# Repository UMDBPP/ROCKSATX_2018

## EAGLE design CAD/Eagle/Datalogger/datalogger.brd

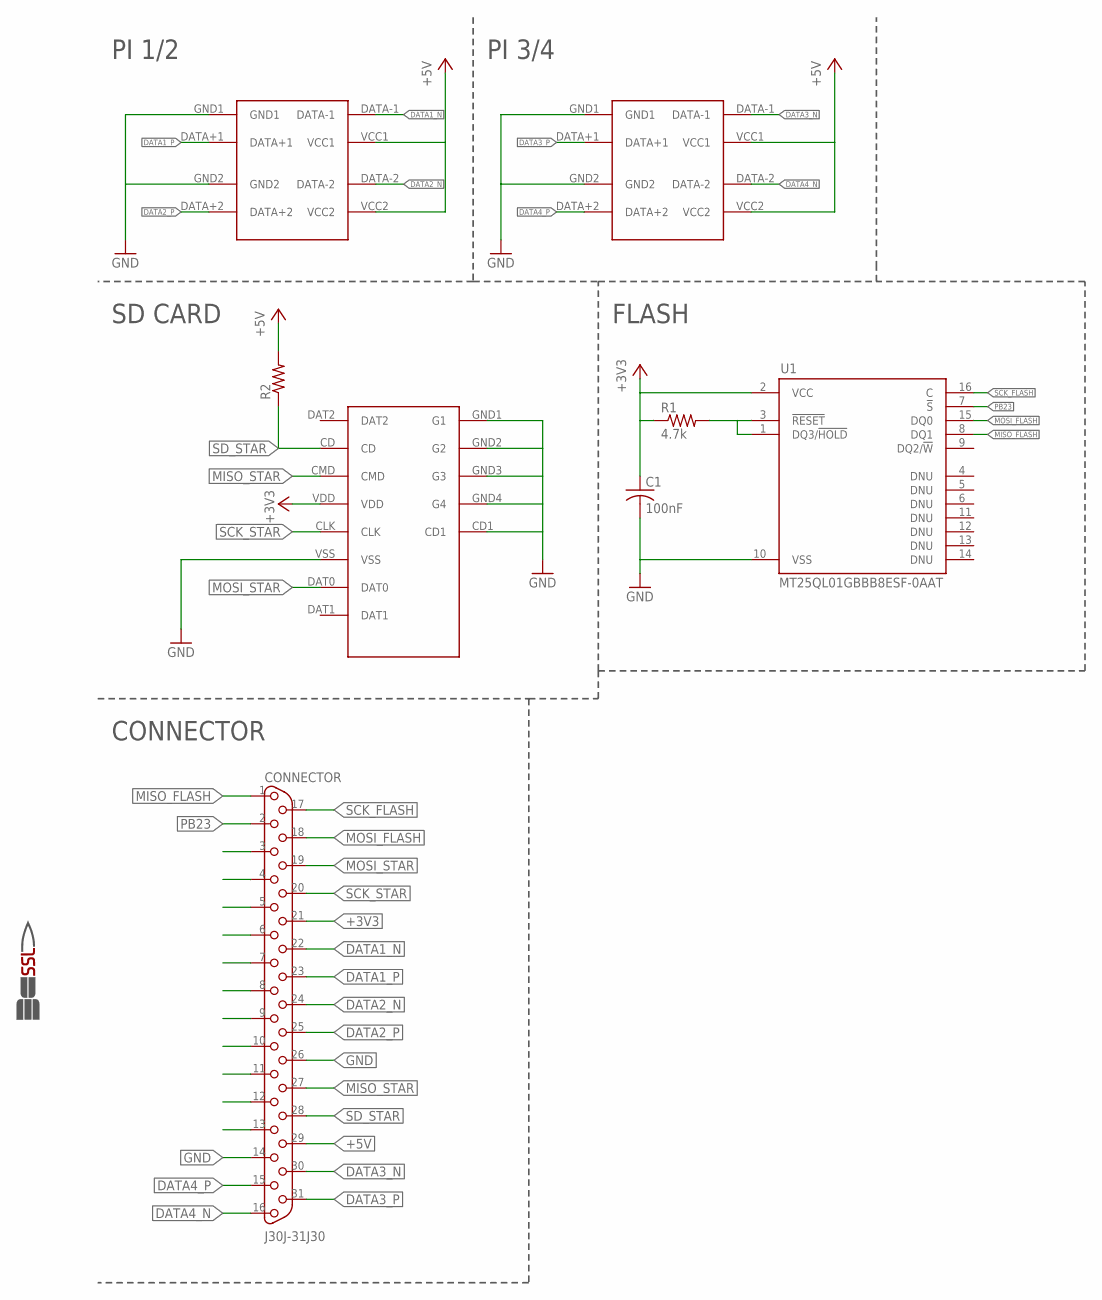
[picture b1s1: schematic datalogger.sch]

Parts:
C1: 100nF; C0603
CONNECTOR: J30J-31J30; ZKN-31-J30
R1: 4.7k; R0603
R2: R-US_R0603; R0603
U1: MT25QL01GBBB8ESF-0AAT; SOP2-16
U$1: MICRO_SD; MICRO_SD_HINGED
U$2, U$3: USB_A
U$4: SSL.3IN_SILK; SSL_SILK_.3IN

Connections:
+3V3: C1.1, CONNECTOR.21, R1.1, U1.2 (VCC), U$1.VDD
+5V: CONNECTOR.29, R2.2, U$2.VCC1, U$2.VCC2, U$3.VCC1, U$3.VCC2
DATA1_N: CONNECTOR.22, U$2.DATA-1
DATA1_P: CONNECTOR.23, U$2.DATA+1
DATA2_N: CONNECTOR.24, U$2.DATA-2
DATA2_P: CONNECTOR.25, U$2.DATA+2
DATA3_N: CONNECTOR.30, U$3.DATA-1
DATA3_P: CONNECTOR.31, U$3.DATA+1
DATA4_N: CONNECTOR.16, U$3.DATA-2
DATA4_P: CONNECTOR.15, U$3.DATA+2
GND: C1.2, CONNECTOR.14, CONNECTOR.26, U1.10 (VSS), U$1.CD1, U$1.GND1 (G1), U$1.GND2 (G2), U$1.GND3 (G3), U$1.GND4 (G4), U$1.VSS, U$2.GND1, U$2.GND2, U$3.GND1, U$3.GND2
MISO_FLASH: CONNECTOR.1, U1.8 (DQ1)
MISO_STAR: CONNECTOR.27, U$1.CMD
MOSI_FLASH: CONNECTOR.18, U1.15 (DQ0)
MOSI_STAR: CONNECTOR.19, U$1.DAT0
unnamed: R1.2, U1.1 (DQ3/!HOLD!), U1.3 (!RESET!)
PB23: CONNECTOR.2, U1.7 (!S!)
SCK_FLASH: CONNECTOR.17, U1.16 (C)
SCK_STAR: CONNECTOR.20, U$1.CLK
SD_STAR: CONNECTOR.28, R2.1, U$1.CD

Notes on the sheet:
PI 1/2
PI 3/4
SD CARD
CONNECTOR
FLASH

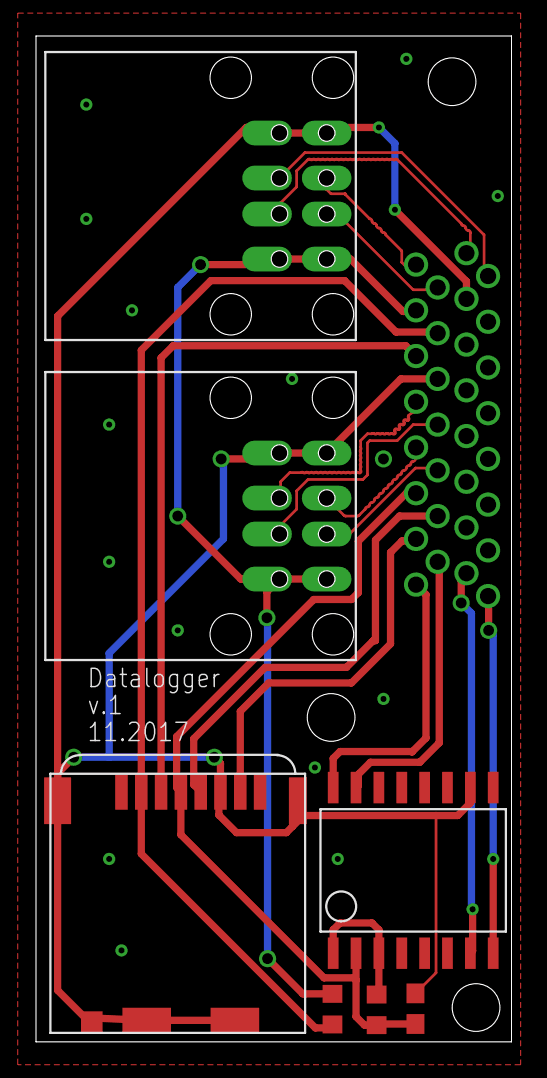
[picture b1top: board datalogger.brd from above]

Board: 2 copper layers, 26.4 x 55.9 mm, 9 parts (1 on the bottom side), 20 nets.

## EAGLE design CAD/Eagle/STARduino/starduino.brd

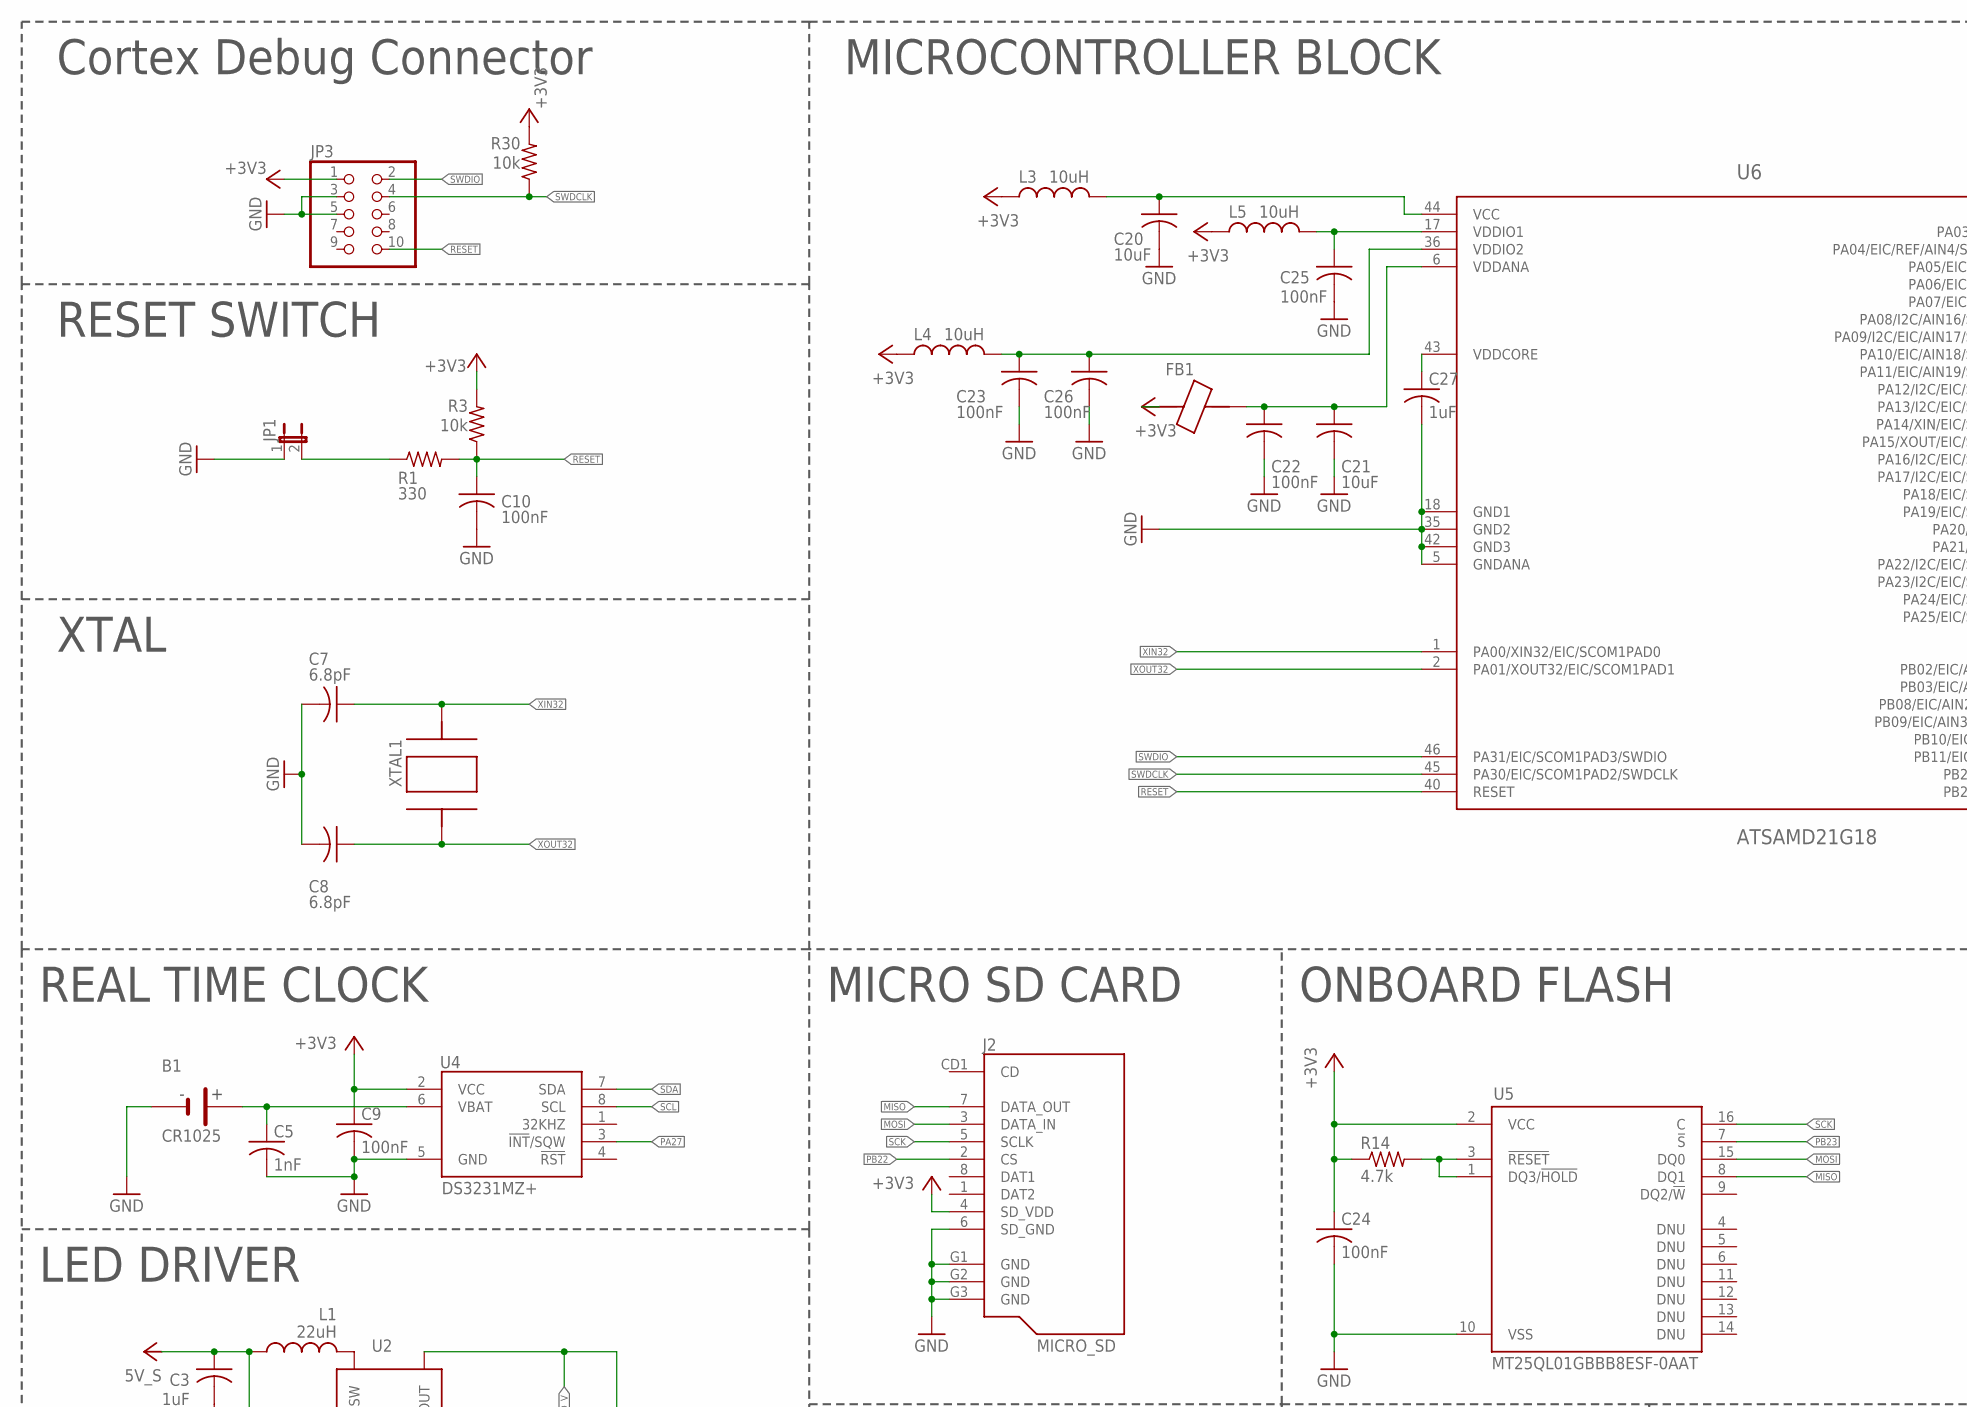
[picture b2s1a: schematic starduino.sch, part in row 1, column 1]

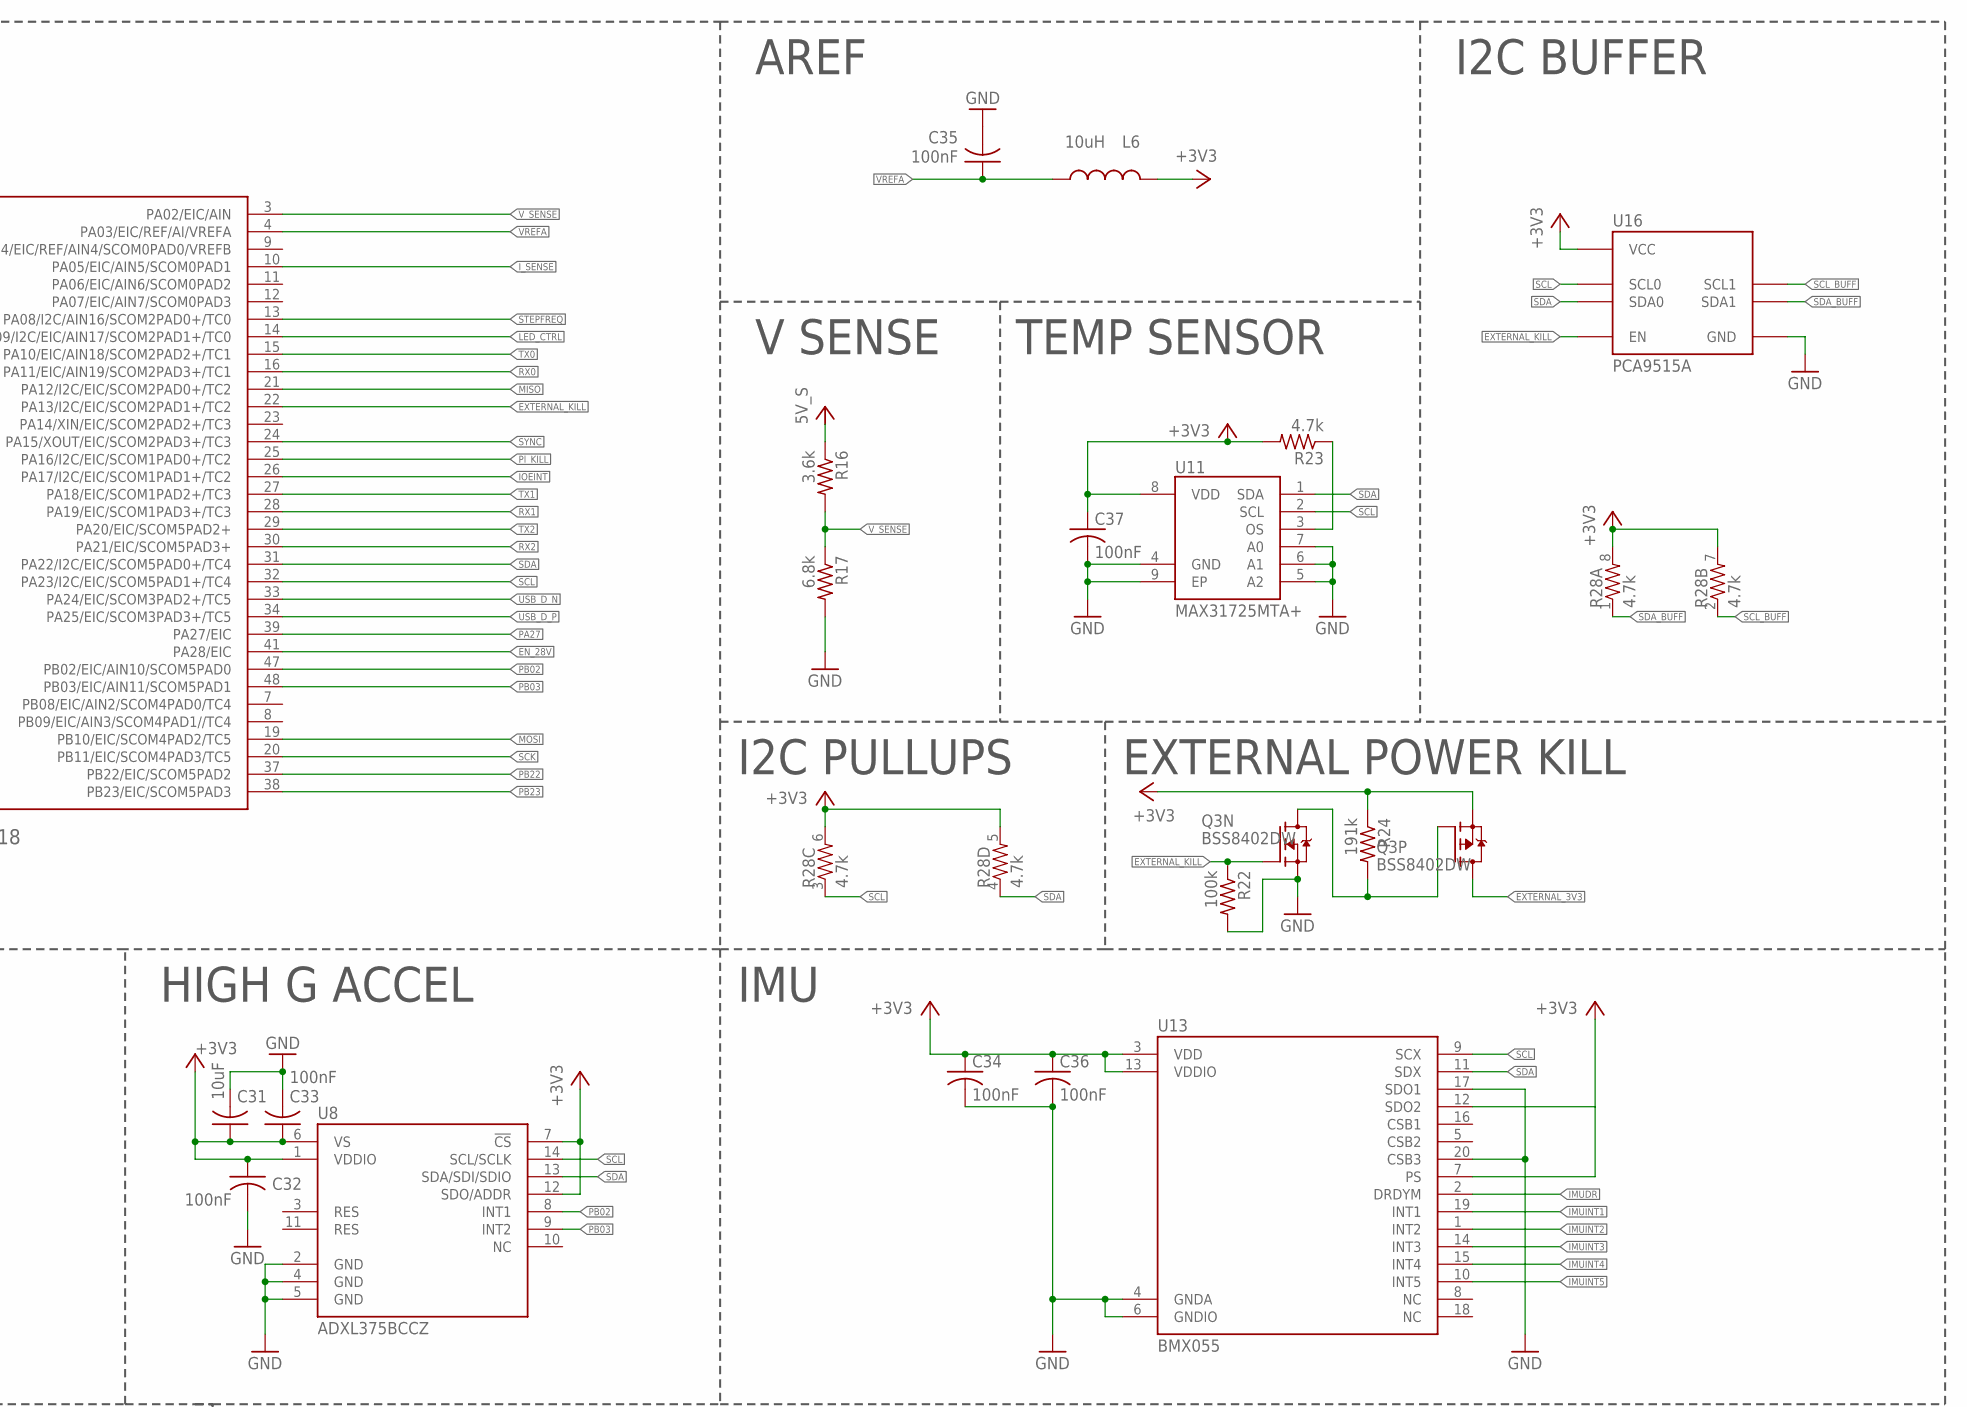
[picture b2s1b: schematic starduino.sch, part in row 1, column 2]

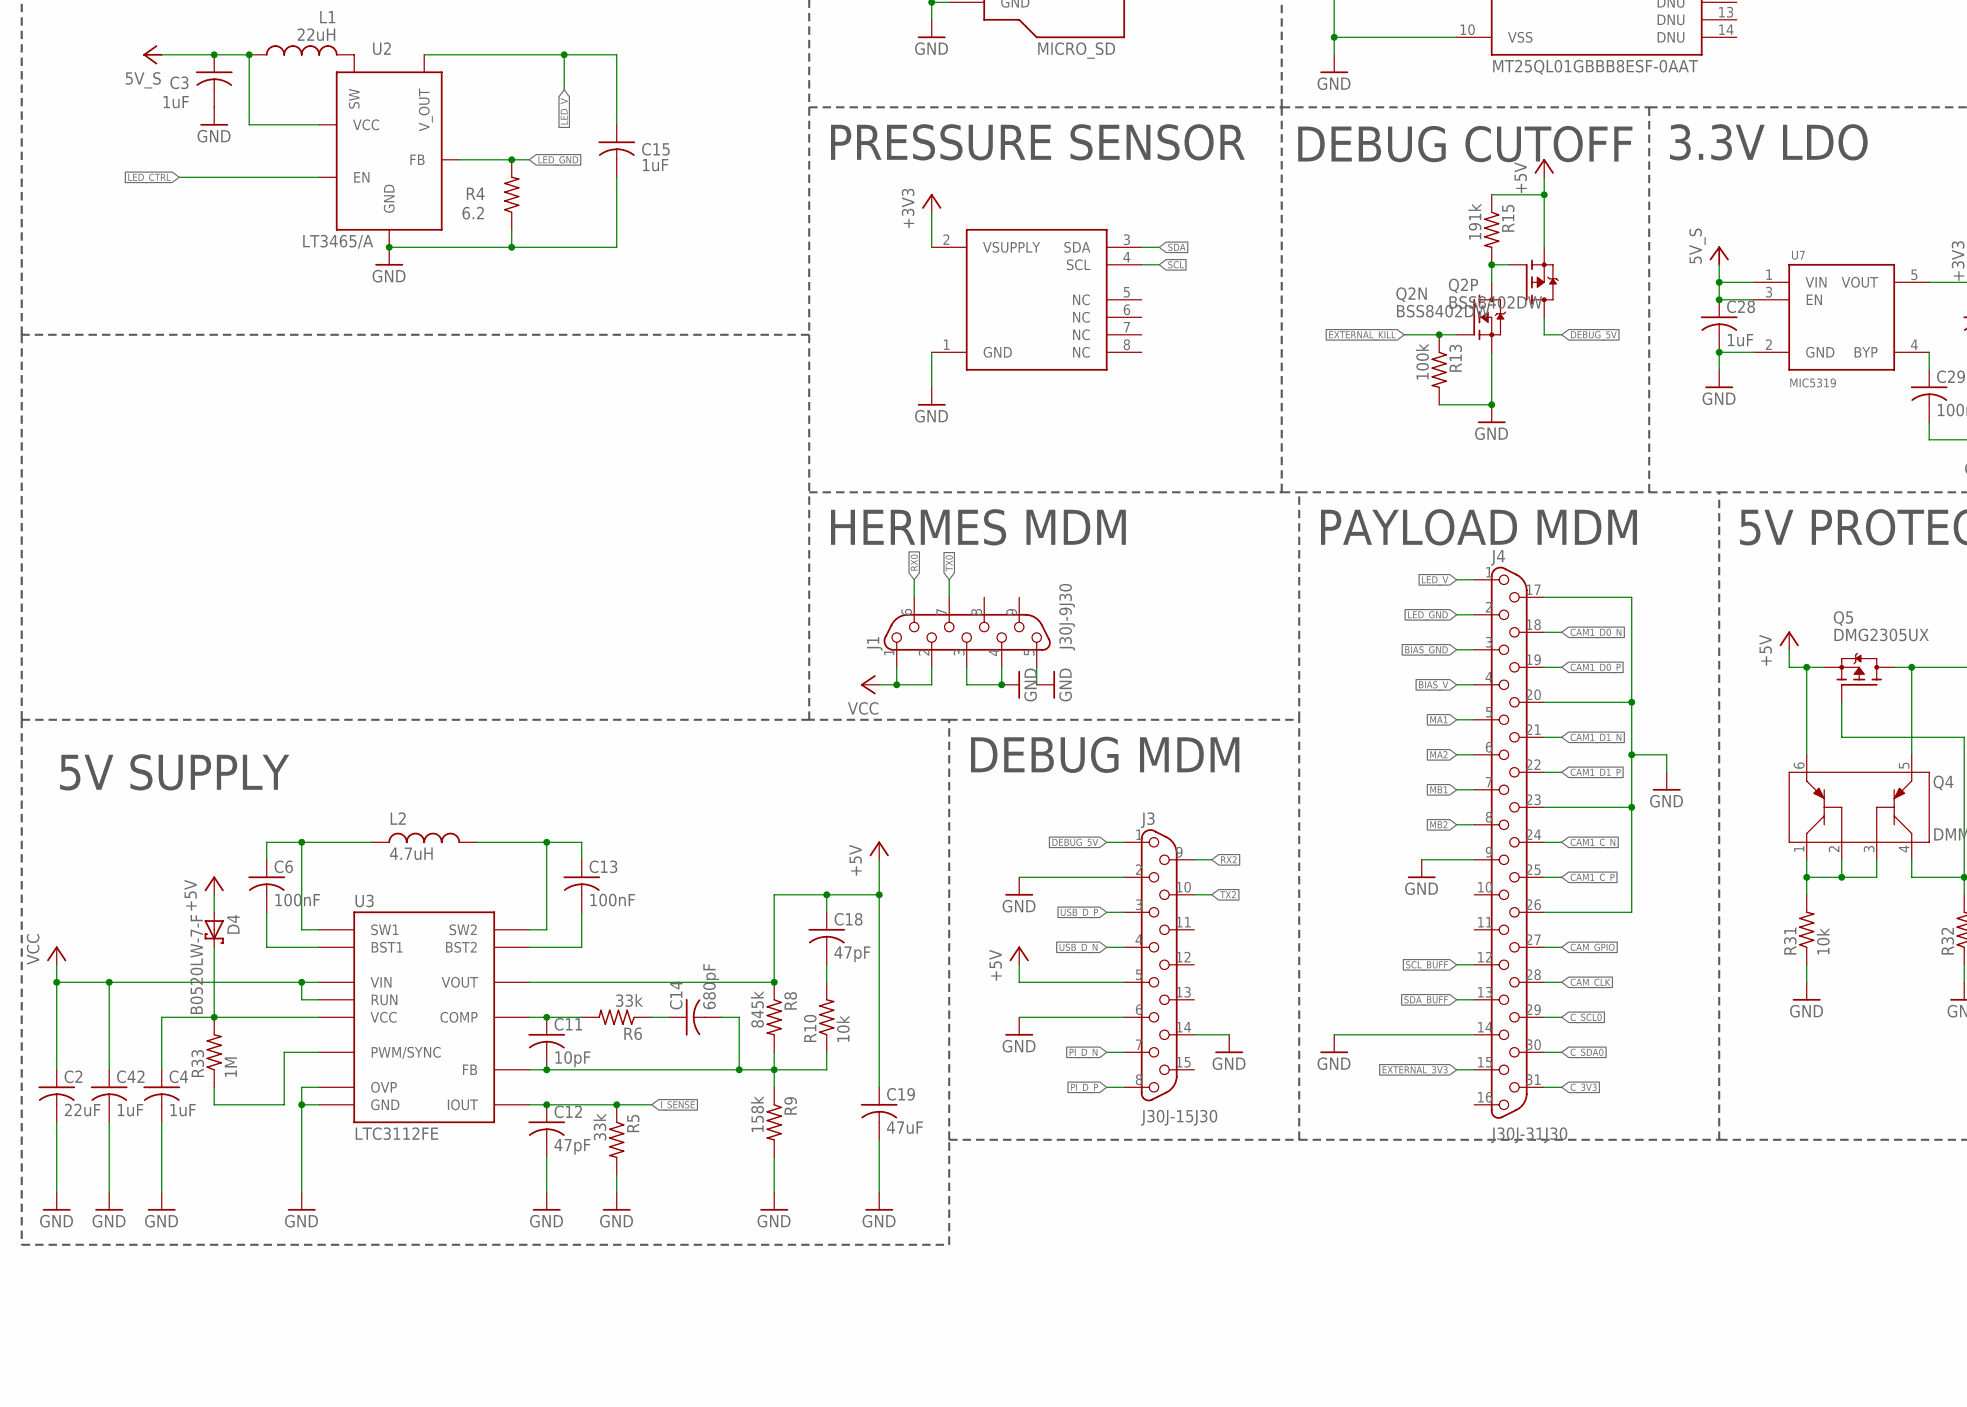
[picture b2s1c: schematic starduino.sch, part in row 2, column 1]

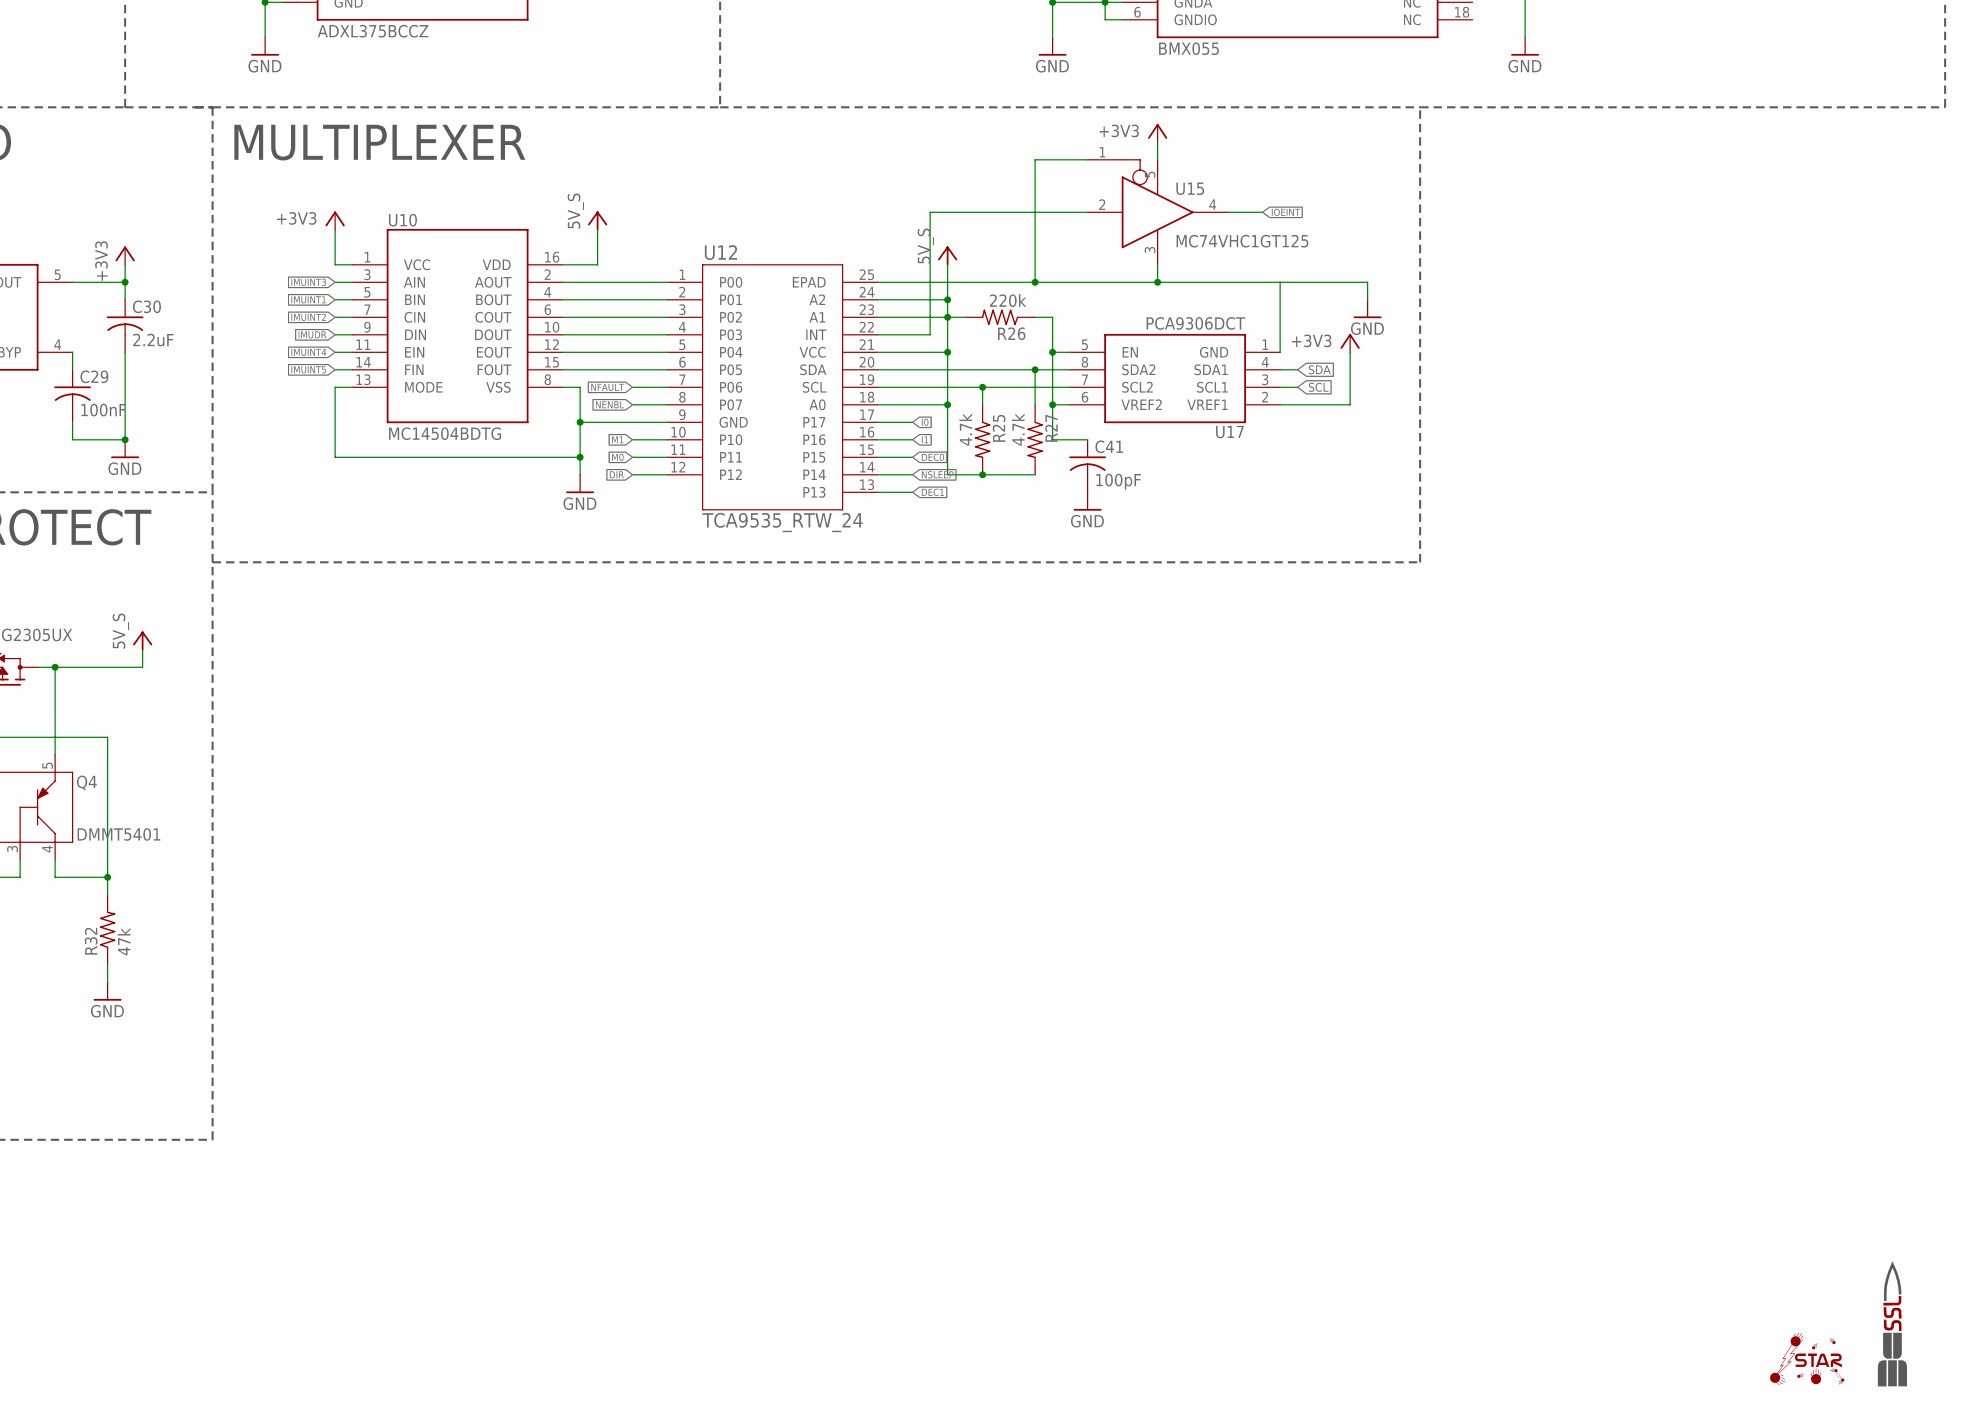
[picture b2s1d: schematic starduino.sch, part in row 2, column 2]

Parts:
B1: CR1025
C2: 22uF; C1206
C3, C4, C15, C27, C28, C42: 1uF; C0603
C5: 1nF; C0603
C6, C9, C10, C13, C22, C23, C24, C25, C26, C29, C32, C33, C34, C35, C36, C37: 100nF; C0603
C7, C8: 6.8pF; C0603
C11: 10pF; C0603
C12, C18: 47pF; C0603
C14: 680pF; C0603
C19: 47uF; C1210
C20, C21, C31: 10uF; C0603
C30: 2.2uF; C0603
C41: 100pF; C0603
D4: B0520LW-7-F; SOD123
FB1: BLM18KG221BH1D; 0603
J1: J30J-9J30; ZKN-9-J30
J2: MICRO_SD; MICROSD_PUSH_PUSH_AMPHENOL
J3: J30J-15J30; ZKN-15-J30
J4: J30J-31J30; ZKN-31-J30
JP1: JUMPER-2PTH; 1X02
JP3: PINHD-2X5; 2X05
L1: 22uH; VLF504012MT(TDK)
L2: 4.7uH; SRP5030
L3, L4, L5, L6: 10uH; 0603
Q2, Q3: BSS8402DW; SC70
Q4: DMMT5401; SOT-26
Q5: DMG2305UX; SOT23
R1: 330; R0603
R3, R10, R30, R31: 10k; R0603
R4: 6.2; R0603
R5, R6: 33k; R0603
R8: 845k; R0603
R9: 158k; R0603
R13, R22: 100k; R0603
R14, R23, R25, R27: 4.7k; R0603
R15, R24: 191k; R0603
R16: 3.6k; R0603
R17: 6.8k; R0603
R26: 220k; R0603
R28: 4.7k; 0603-ARV
R32: 47k; R0603
R33: 1M; R0603
U1: SSCMNNN015PA2A3; HSC-SMT-8
U2: LT3465/A; SOT23-6
U3: LTC3112FE; TSSOP20
U4: DS3231MZ+; SOIC-8
U5: MT25QL01GBBB8ESF-0AAT; SOP2-16
U6: ATSAMD21G18; 48-TQFP
U7: MIC5319; SOT23-5L
U8: ADXL375BCCZ; LGA-14
U10: MC14504BDTG; TSSOP16
U11: MAX31725MTA+; DFN-8
U12: TCA9535_RTW_24; RTW24_2P45X2P45
U13: BMX055; LGA-20
U15: MC74VHC1GT125; SC-70-5
U16: PCA9515A; TSSOP8
U17: PCA9306DCT; SSOP8
U$1: STAR; STAR_.3IN
U$2: SSL.3IN_SILK; SSL_SILK_.3IN
XTAL1: ABS07AIG-32.768KHZ-1-T; 2-SMD

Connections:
5V_S: C3.1, C28.1, L1.P$1 (1), Q4.5 (E2), Q5.3 (D), R16.1, R25.2, R26.2, R27.2, U2.5 (VCC), U7.1 (VIN), U7.3 (EN), U10.16 (VDD), U12.18 (A0), U12.21 (VCC), U12.23 (A1), U12.24 (A2)
+3V3: C9.1, C24.1, C30.1, C31.1, C32.1, C33.1, C34.1, C36.1, C37.1, FB1.1, J2.4 (SD_VDD), JP3.1, L3.1, L4.1, L5.1, L6.2, Q3.4 (S), R3.2, R14.1, R23.2, R24.1, R28.5 (2), R28.6 (2), R28.7 (2), R28.8 (2), R30.2, U1.2 (VSUPPLY), U4.2 (VCC), U5.2 (VCC), U7.5 (VOUT), U8.1 (VDDIO), U8.6 (VS), U8.7 (!CS!), U8.12 (SDO/ADDR), U10.1 (VCC), U11.8 (VDD), U13.3 (VDD), U13.7 (PS), U13.12 (SDO2), U13.13 (VDDIO), U15.5 (VIN), U16.P$8 (VCC), U17.2 (VREF1)
+5V: C18.1, C19.1, D4.A, J3.5, Q2.4 (S), Q4.6 (E1), Q5.2 (S), R8.1, R15.1, U3.9 (VOUT)
BIAS_GND: J4.3
BIAS_V: J4.4
CAM1_C_N: J4.24
CAM1_C_P: J4.25
CAM1_D0_N: J4.18
CAM1_D0_P: J4.19
CAM1_D1_N: J4.21
CAM1_D1_P: J4.22
CAM_CLK: J4.28
CAM_GPIO: J4.27
C_3V3: J4.31
C_SCL0: J4.29
C_SDA0: J4.30
DEBUG_5V: J3.1, Q2.3 (D)
DEC0: U12.15
DEC1: U12.13
DIR: U12.12
EN_28V: U6.41 (PA28/EIC)
EXTERNAL_3V3: J4.15, Q3.3 (D)
EXTERNAL_KILL: Q2.2 (G), Q3.2 (G), R13.1, R22.1, U6.22 (PA13/I2C/EIC/SCOM2PAD1+/TC2), U16.P$5 (EN)
FB_5: C11.2, C14.2, R8.2, R9.1, R10.1, U3.3 (FB)
GND: B1.3 (-), C2.2, C3.2, C4.2, C5.2, C7.2, C8.2, C9.2, C10.2, C12.2, C15.2, C19.2, C20.2, C21.2, C22.2, C23.2, C24.2, C25.2, C26.2, C27.2, C28.2, C29.2, C30.2, C31.2, C32.2, C33.2, C34.2, C35.2, C36.2, C37.2, C41.2, C42.2, J1.3, J1.4, J1.5, J2.6 (SD_GND), J2.G1 (GND), J2.G2 (GND), J2.G3 (GND), J3.2, J3.6, J3.14, J4.9, J4.14, J4.17, J4.20, J4.23, J4.26, JP1.1, JP3.3, JP3.5, Q2.1 (S), Q3.1 (S), R4.1, R5.2, R9.2, R13.2, R17.2, R22.2, R31.1, R32.1, U1.1 (GND), U2.2 (GND), U3.1 (GND), U3.4 (OVP), U3.10 (GND), U3.11 (GND), U3.20 (GND), U3.PAD (GND), U4.5 (GND), U5.10 (VSS), U6.5 (GNDANA), U6.18 (GND1), U6.35 (GND2), U6.42 (GND3), U7.2 (GND), U8.2 (GND), U8.4 (GND), U8.5 (GND), U10.8 (VSS), U10.13 (MODE), U11.4 (GND), U11.5 (A2), U11.6 (A1), U11.7 (A0), U11.9 (EP), U12.9 (GND), U12.25 (EPAD), U13.4 (GNDA), U13.6 (GNDIO), U13.17 (SDO1), U13.20 (CSB3), U15.1 (OE), U15.3 (GND), U16.P$4 (GND), U17.1 (GND)
I0: U12.17
I1: U12.16
IMUDR: U10.9 (DIN), U13.2 (DRDYM)
IMUINT1: U10.5 (BIN), U13.19 (INT1)
IMUINT2: U10.7 (CIN), U13.1 (INT2)
IMUINT3: U10.3 (AIN), U13.14 (INT3)
IMUINT4: U10.11 (EIN), U13.15 (INT4)
IMUINT5: U10.14 (FIN), U13.10 (INT5)
IOEINT: U6.26 (PA17/I2C/EIC/SCOM1PAD1+/TC2), U15.4 (Y)
I_SENSE: C12.1, R5.1, U3.8 (IOUT), U6.10 (PA05/EIC/AIN5/SCOM0PAD1)
LED_CTRL: U2.4 (EN), U6.14 (PA09/I2C/EIC/AIN17/SCOM2PAD1+/TC0)
LED_GND: J4.2, R4.2, U2.3 (FB)
LED_V: C15.1, J4.1, U2.1 (V_OUT)
M0: U12.11
M1: U12.10
MA1: J4.5
MA2: J4.6
MB1: J4.7
MB2: J4.8
MISO: J2.7 (DATA_OUT), U5.8 (DQ1), U6.21 (PA12/I2C/EIC/SCOM2PAD0+/TC2)
MOSI: J2.3 (DATA_IN), U5.15 (DQ0), U6.19 (PB10/EIC/SCOM4PAD2/TC5)
unnamed: Q4.4 (C2), Q5.1 (G), R32.2
unnamed: Q4.1 (C1), Q4.2 (B1), Q4.3 (B2), R31.2
unnamed: R33.1, U3.19 (PWM/SYNC)
unnamed: C25.1, L5.2, U6.17 (VDDIO1)
unnamed: C27.1, U6.43 (VDDCORE)
unnamed: R23.1, U11.3 (OS)
unnamed: JP1.2, R1.1
unnamed: B1.1 (+), B1.2 (+), C5.1, U4.6 (VBAT)
unnamed: C29.1, U7.4 (BYP)
unnamed: C21.1, C22.1, FB1.2, U6.6 (VDDANA)
unnamed: C14.1, R6.1
unnamed: C11.1, R6.2, U3.2 (COMP)
unnamed: C20.1, L3.2, U6.44 (VCC)
unnamed: L1.P$2 (2), U2.6 (SW)
unnamed: Q3.5 (G), Q3.6 (D), R24.2
unnamed: U10.2 (AOUT), U12.1 (P00)
unnamed: U10.4 (BOUT), U12.2 (P01)
unnamed: C23.1, C26.1, L4.2, U6.36 (VDDIO2)
unnamed: U12.22 (INT), U15.2 (A)
unnamed: U10.6 (COUT), U12.3 (P02)
unnamed: U10.10 (DOUT), U12.4 (P03)
unnamed: U10.12 (EOUT), U12.5 (P04)
unnamed: U10.15 (FOUT), U12.6 (P05)
unnamed: R14.2, U5.1 (DQ3/!HOLD!), U5.3 (!RESET!)
unnamed: R27.1, U12.20 (SDA), U17.8 (SDA2)
unnamed: R25.1, U12.19 (SCL), U17.7 (SCL2)
unnamed: C41.1, R26.1, U17.5 (EN), U17.6 (VREF2)
unnamed: Q2.5 (G), Q2.6 (D), R15.2
unnamed: C6.1, L2.P$1, U3.15 (SW1), U3.16 (SW1)
unnamed: C13.1, L2.P$2, U3.12 (SW2), U3.13 (SW2)
unnamed: C6.2, U3.17 (BST1)
unnamed: C13.2, U3.14 (BST2)
unnamed: C4.1, D4.C, R33.2, U3.18 (VCC)
unnamed: C18.2, R10.2
NENBL: U12.8 (P07)
NFAULT: U12.7 (P06)
NSLEEP: U12.14
PA27: U4.3 (!INT!/SQW), U6.39 (PA27/EIC)
PB02: U6.47 (PB02/EIC/AIN10/SCOM5PAD0), U8.8 (INT1)
PB03: U6.48 (PB03/EIC/AIN11/SCOM5PAD1), U8.9 (INT2)
PB22: J2.2 (CS), U6.37 (PB22/EIC/SCOM5PAD2)
PB23: U5.7 (!S!), U6.38 (PB23/EIC/SCOM5PAD3)
PI_D_N: J3.7
PI_D_P: J3.8
PI_KILL: U6.25 (PA16/I2C/EIC/SCOM1PAD0+/TC2)
RESET: C10.1, JP3.10, R1.2, R3.1, U6.40 (RESET)
RX0: J1.6, U6.16 (PA11/EIC/AIN19/SCOM2PAD3+/TC1)
RX1: U6.28 (PA19/EIC/SCOM1PAD3+/TC3)
RX2: J3.9, U6.30 (PA21/EIC/SCOM5PAD3+)
SCK: J2.5 (SCLK), U5.16 (C), U6.20 (PB11/EIC/SCOM4PAD3/TC5)
SCL: R28.3 (1), U1.4 (SCL), U4.8 (SCL), U6.32 (PA23/I2C/EIC/SCOM5PAD1+/TC4), U8.14 (SCL/SCLK), U11.2 (SCL), U13.9 (SCX), U16.P$2 (SCL0), U17.3 (SCL1)
SCL_BUFF: J4.12, R28.2 (1), U16.P$7 (SCL1)
SDA: R28.4 (1), U1.3 (SDA), U4.7 (SDA), U6.31 (PA22/I2C/EIC/SCOM5PAD0+/TC4), U8.13 (SDA/SDI/SDIO), U11.1 (SDA), U13.11 (SDX), U16.P$3 (SDA0), U17.4 (SDA1)
SDA_BUFF: J4.13, R28.1, U16.P$6 (SDA1)
STEPFREQ: U6.13 (PA08/I2C/AIN16/SCOM2PAD0+/TC0)
SWDCLK: JP3.4, R30.1, U6.45 (PA30/EIC/SCOM1PAD2/SWDCLK)
SWDIO: JP3.2, U6.46 (PA31/EIC/SCOM1PAD3/SWDIO)
SYNC: U6.24 (PA15/XOUT/EIC/SCOM2PAD3+/TC3)
TX0: J1.7, U6.15 (PA10/EIC/AIN18/SCOM2PAD2+/TC1)
TX1: U6.27 (PA18/EIC/SCOM1PAD2+/TC3)
TX2: J3.10, U6.29 (PA20/EIC/SCOM5PAD2+)
USB_D_N: J3.4, U6.33 (PA24/EIC/SCOM3PAD2+/TC5)
USB_D_P: J3.3, U6.34 (PA25/EIC/SCOM3PAD3+/TC5)
VCC: C2.1, C42.1, J1.1, J1.2, U3.5 (VIN), U3.6 (VIN), U3.7 (RUN)
VREFA: C35.1, L6.1, U6.4 (PA03/EIC/REF/AI/VREFA)
V_SENSE: R16.2, R17.1, U6.3 (PA02/EIC/AIN)
XIN32: C7.1, U6.1 (PA00/XIN32/EIC/SCOM1PAD0), XTAL1.P2 (2)
XOUT32: C8.1, U6.2 (PA01/XOUT32/EIC/SCOM1PAD1), XTAL1.P1 (1)

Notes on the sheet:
MICROCONTROLLER BLOCK
Cortex Debug Connector
RESET SWITCH
XTAL
AREF
V SENSE
I2C PULLUPS
HIGH G ACCEL
TEMP SENSOR
REAL TIME CLOCK
IMU
MICRO SD CARD
ONBOARD FLASH
LED DRIVER
MULTIPLEXER
DEBUG CUTOFF
I2C BUFFER
EXTERNAL POWER KILL
3.3V LDO
5V SUPPLY
HERMES MDM
DEBUG MDM
PAYLOAD MDM
5V PROTECT
PRESSURE SENSOR

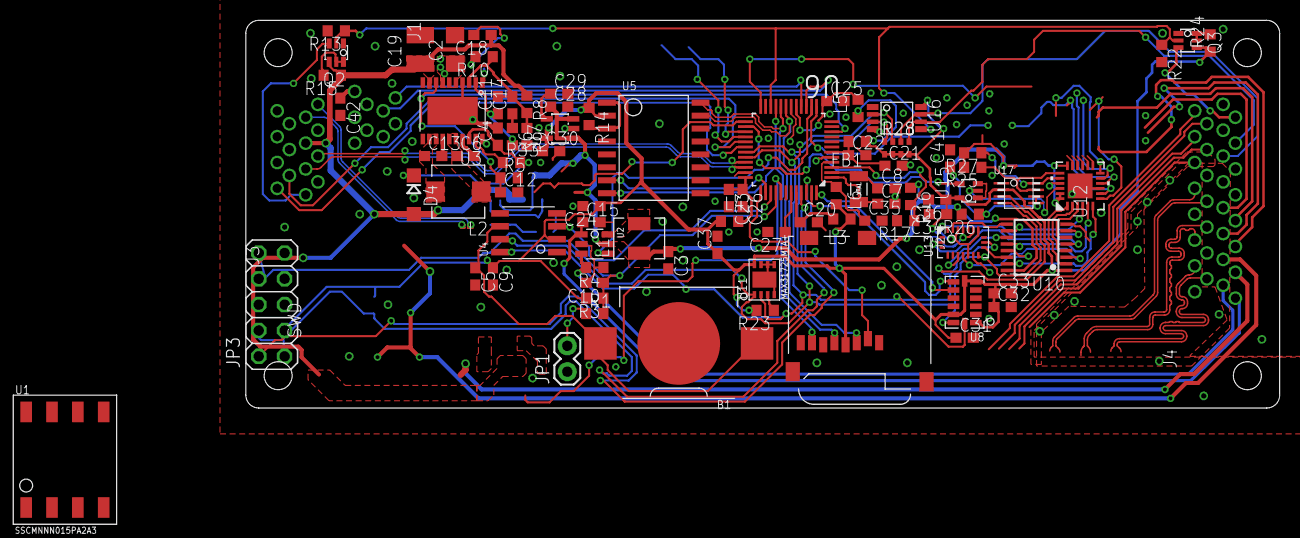
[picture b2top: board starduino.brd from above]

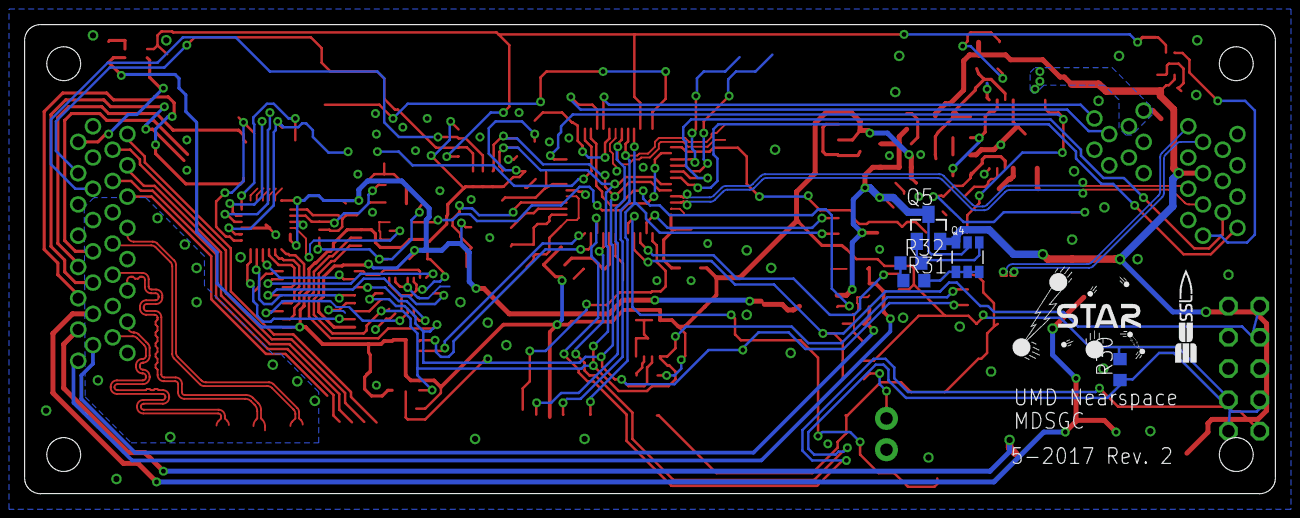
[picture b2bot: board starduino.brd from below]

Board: 2 copper layers, 101.6 x 38.1 mm, 97 parts (7 on the bottom side), 79 nets.

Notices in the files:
parts and their libraries:
SparkFun-Passives: Licensing: CC v3.0 Share-Alike You are welcome to use this library for commercial purposes.
